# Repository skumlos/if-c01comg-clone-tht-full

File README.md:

IF-C01COMG Clone board THT Full size

This is a full sized version of the IF-C01COMG board for JVC pro monitors (TM-Hxx50CG) and some others...

It's basically the THT base board I made some years ago with SCART or BNC input and some audio mixing
stuff.

Credit goes to James Vanderloeff for the dual input idea.

You can upload the zip file from the plot directory directly to manufacturers that don't do kicad files directly.

You're welcome to clone, sell, re-design and whatever, see LICENSE.

(2020) Martin Hejnfelt (martin@hejnfelt.com)
This work is free. You can redistribute it and/or modify it under the
terms of the Do What The Fuck You Want To Public License, Version 2,
as published by Sam Hocevar. See the LICENSE file for more details.

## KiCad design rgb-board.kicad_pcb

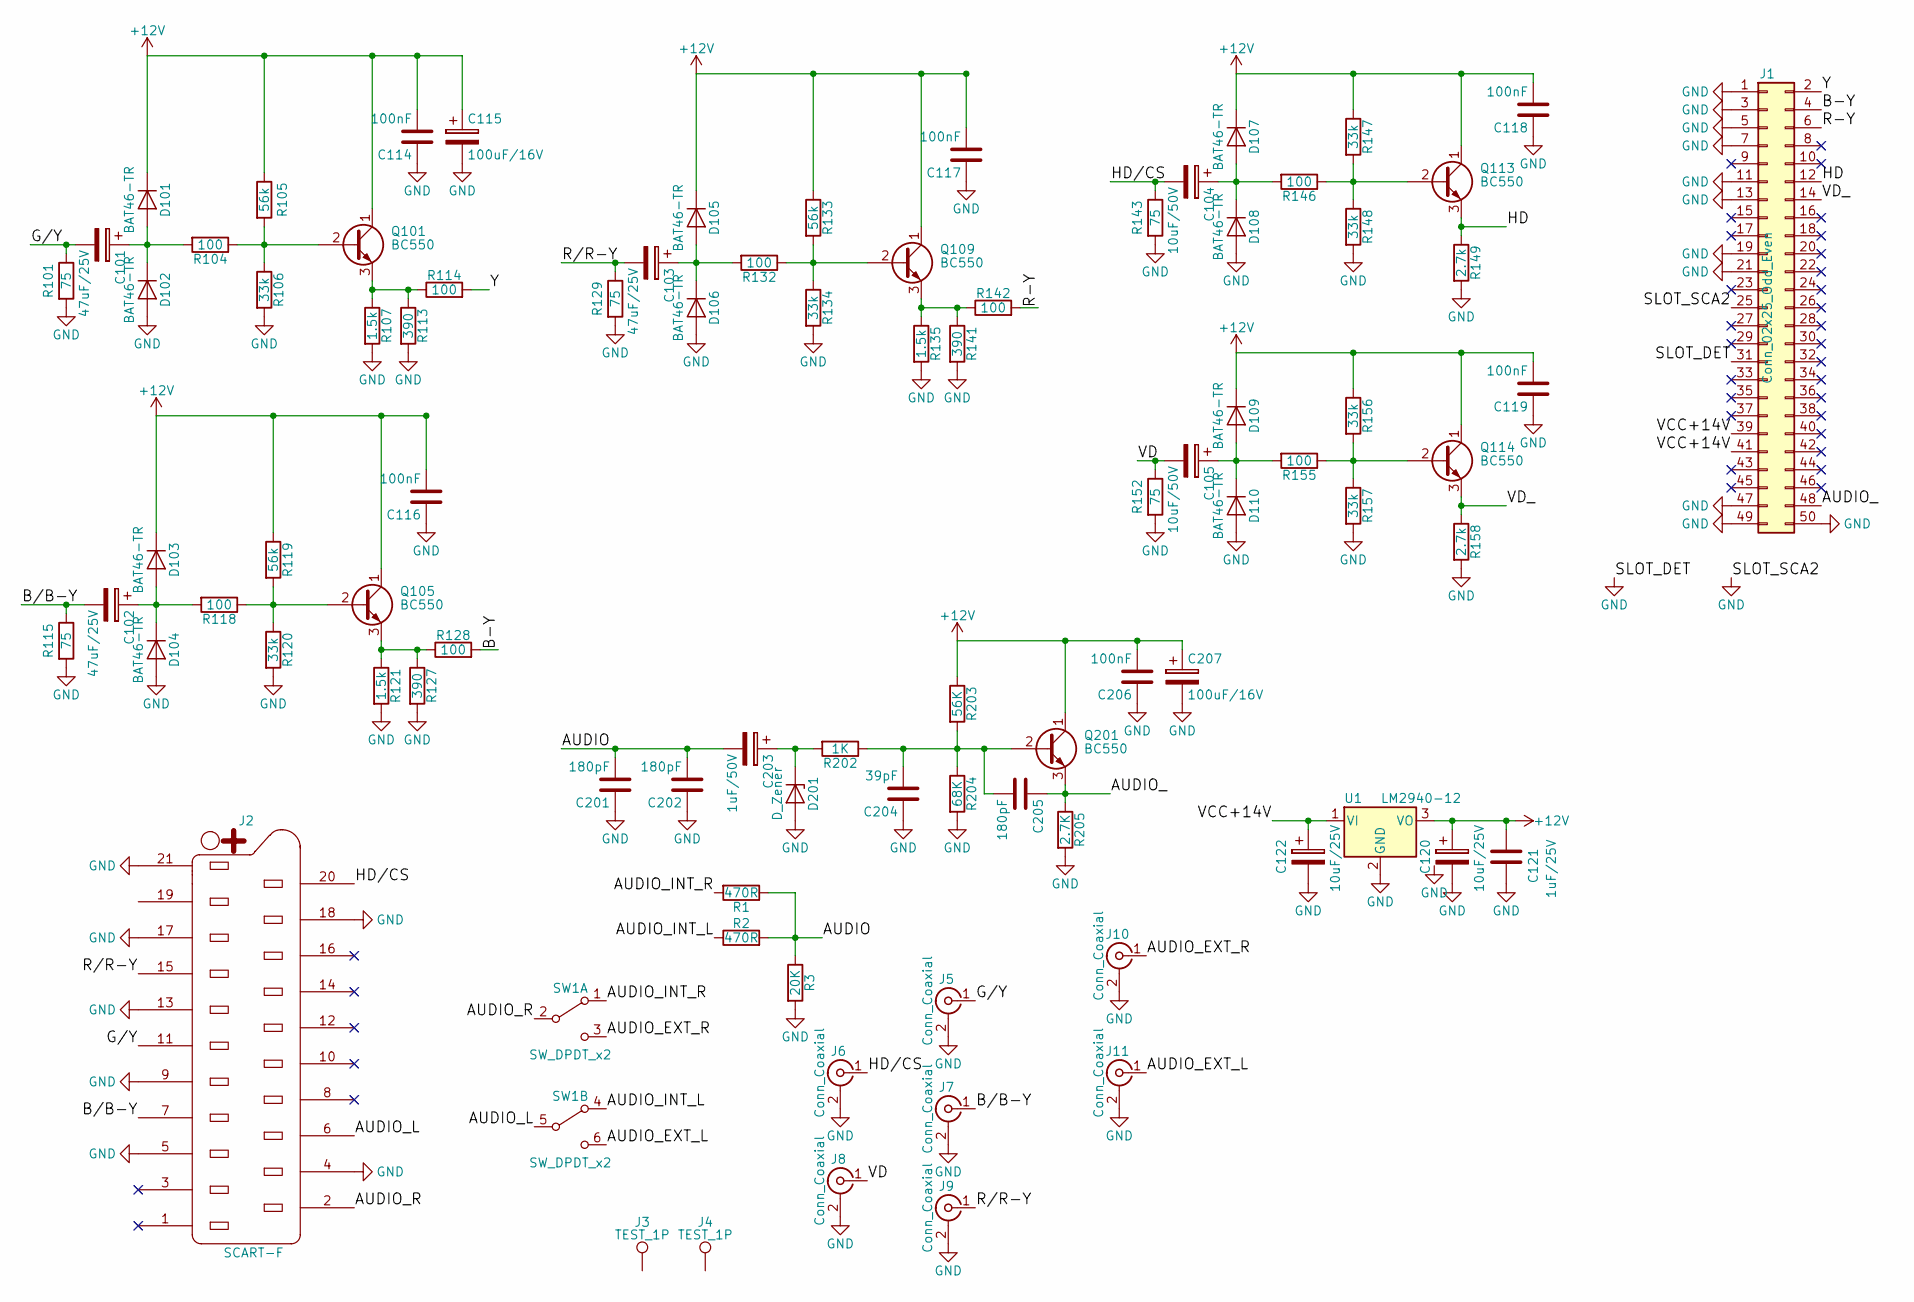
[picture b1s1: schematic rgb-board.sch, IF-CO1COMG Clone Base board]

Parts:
C101, C102, C103: 47uF/25V; CP_Radial_D5.0mm_P2.50mm
C104, C105: 10uF/50V; CP_Radial_D5.0mm_P2.00mm
C114, C116, C117, C118, C119, C206: 100nF; C_Disc_D3.8mm_W2.6mm_P2.50mm
C115, C207: 100uF/16V; CP_Radial_D6.3mm_P2.50mm
C120, C122: 10uF/25V; CP_Radial_D5.0mm_P2.00mm
C121: 1uF/25V; C_Disc_D5.0mm_W2.5mm_P2.50mm
C201, C202, C205: 180pF; C_Disc_D3.8mm_W2.6mm_P2.50mm
C203: 1uF/50V; CP_Radial_D5.0mm_P2.50mm
C204: 39pF; C_Disc_D3.8mm_W2.6mm_P2.50mm
D101, D102, D103, D104, D105, D106, D107, D108, D109, D110: BAT46-TR; D_DO-35_SOD27_P7.62mm_Horizontal
D201: D_Zener; D_DO-35_SOD27_P7.62mm_Horizontal
J1: Conn_02x25_Odd_Even; Pin_Header_Angled_2x25_Pitch2.54mm
J2: SCART-F; NINIGI-SCART-RA
J3, J4: TEST_1P; MountingHole_3.2mm_M3
J5, J6, J7, J8, J9: Conn_Coaxial; BNC-THT
J10, J11: Conn_Coaxial; RCJ-04X
Q101, Q105, Q109, Q113, Q114, Q201: BC550; TO-92_Molded_Narrow
R1, R2: 470R; R_Axial_DIN0207_L6.3mm_D2.5mm_P7.62mm_Horizontal
R3: 20K; R_Axial_DIN0207_L6.3mm_D2.5mm_P7.62mm_Horizontal
R101, R115, R129, R143, R152: 75; R_Axial_DIN0207_L6.3mm_D2.5mm_P7.62mm_Horizontal
R104, R114, R118, R128, R132, R142, R146, R155: 100; R_Axial_DIN0207_L6.3mm_D2.5mm_P7.62mm_Horizontal
R105, R119, R133: 56k; R_Axial_DIN0207_L6.3mm_D2.5mm_P7.62mm_Horizontal
R106, R120, R134, R147, R148, R156, R157: 33k; R_Axial_DIN0207_L6.3mm_D2.5mm_P7.62mm_Horizontal
R107, R121, R135: 1.5k; R_Axial_DIN0207_L6.3mm_D2.5mm_P7.62mm_Horizontal
R113, R127, R141: 390; R_Axial_DIN0207_L6.3mm_D2.5mm_P7.62mm_Horizontal
R149, R158: 2.7k; R_Axial_DIN0207_L6.3mm_D2.5mm_P7.62mm_Horizontal
R202: 1K; R_Axial_DIN0207_L6.3mm_D2.5mm_P7.62mm_Horizontal
R203: 56K; R_Axial_DIN0207_L6.3mm_D2.5mm_P7.62mm_Horizontal
R204: 68K; R_Axial_DIN0207_L6.3mm_D2.5mm_P7.62mm_Horizontal
R205: 2.7K; R_Axial_DIN0207_L6.3mm_D2.5mm_P7.62mm_Horizontal
SW1: SW_DPDT_x2; LC2259
U1: LM2940-12; TO-220_Horizontal

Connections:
+12V: C114.2, C115.1, C116.2, C117.2, C118.2, C119.2, C120.1, C121.2, C206.2, C207.1, D101.1 (K), D103.1 (K), D105.1 (K), D107.1 (K), D109.1 (K), Q101.1 (C), Q105.1 (C), Q109.1 (C), Q113.1 (C), Q114.1 (C), Q201.1 (C), R105.1, R119.1, R133.1, R147.1, R156.1, R203.1, U1.3 (VO)
/AUDIO: C201.2, C202.2, C203.2, R1.1, R2.2, R3.1
/AUDIO_: C205.1, J1.48, Q201.3 (E), R205.1
/AUDIO_EXT_L: J11.1 (In), SW1.6 (C)
/AUDIO_EXT_R: J10.1 (In), SW1.3 (C)
/AUDIO_INT_L: R2.1, SW1.4 (A)
/AUDIO_INT_R: R1.2, SW1.1 (A)
/AUDIO_L: J2.6, SW1.5 (B)
/AUDIO_R: J2.2, SW1.2 (B)
/B-Y: J1.4, R128.2
/B/B-Y: C102.2, J2.7, J7.1 (In), R115.1
/G/Y: C101.2, J2.11, J5.1 (In), R101.1
/HD: J1.12, Q113.3 (E), R149.1
/HD/CS: C104.2, J2.20, J6.1 (In), R143.1
/R-Y: J1.6, R142.2
/R/R-Y: C103.2, J2.15, J9.1 (In), R129.1
/VCC+14V: C122.1, J1.39, J1.41, U1.1 (VI)
/VD: C105.2, J8.1 (In), R152.1
/VD_: J1.14, Q114.3 (E), R158.1
/Y: J1.2, R114.2
GND: C114.1, C115.2, C116.1, C117.1, C118.1, C119.1, C120.2, C121.1, C122.2, C201.1, C202.1, C204.1, C206.1, C207.2, D102.2 (A), D104.2 (A), D106.2 (A), D108.2 (A), D110.2 (A), D201.2 (A), J1.1, J1.3, J1.5, J1.7, J1.11, J1.13, J1.19, J1.21, J1.25, J1.31, J1.47, J1.49, J1.50, J2.4, J2.5, J2.9, J2.13, J2.17, J2.18, J2.21, J5.2 (Ext), J6.2 (Ext), J7.2 (Ext), J8.2 (Ext), J9.2 (Ext), J10.2 (Ext), J11.2 (Ext), R3.2, R101.2, R106.2, R107.2, R113.2, R115.2, R120.2, R121.2, R127.2, R129.2, R134.2, R135.2, R141.2, R143.2, R148.2, R149.2, R152.2, R157.2, R158.2, R204.2, R205.2, U1.2 (GND)
unnamed: C101.1, D101.2 (A), D102.1 (K), R104.2
unnamed: C102.1, D103.2 (A), D104.1 (K), R118.2
unnamed: C103.1, D105.2 (A), D106.1 (K), R132.2
unnamed: C104.1, D107.2 (A), D108.1 (K), R146.2
unnamed: C105.1, D109.2 (A), D110.1 (K), R155.2
unnamed: C203.1, D201.1 (K), R202.2
unnamed: C204.2, C205.2, Q201.2 (B), R202.1, R203.2, R204.1
unnamed: Q101.2 (B), R104.1, R105.2, R106.1
unnamed: Q101.3 (E), R107.1, R113.1, R114.1
unnamed: Q105.2 (B), R118.1, R119.2, R120.1
unnamed: Q105.3 (E), R121.1, R127.1, R128.1
unnamed: Q109.2 (B), R132.1, R133.2, R134.1
unnamed: Q109.3 (E), R135.1, R141.1, R142.1
unnamed: Q113.2 (B), R146.1, R147.2, R148.1
unnamed: Q114.2 (B), R155.1, R156.2, R157.1

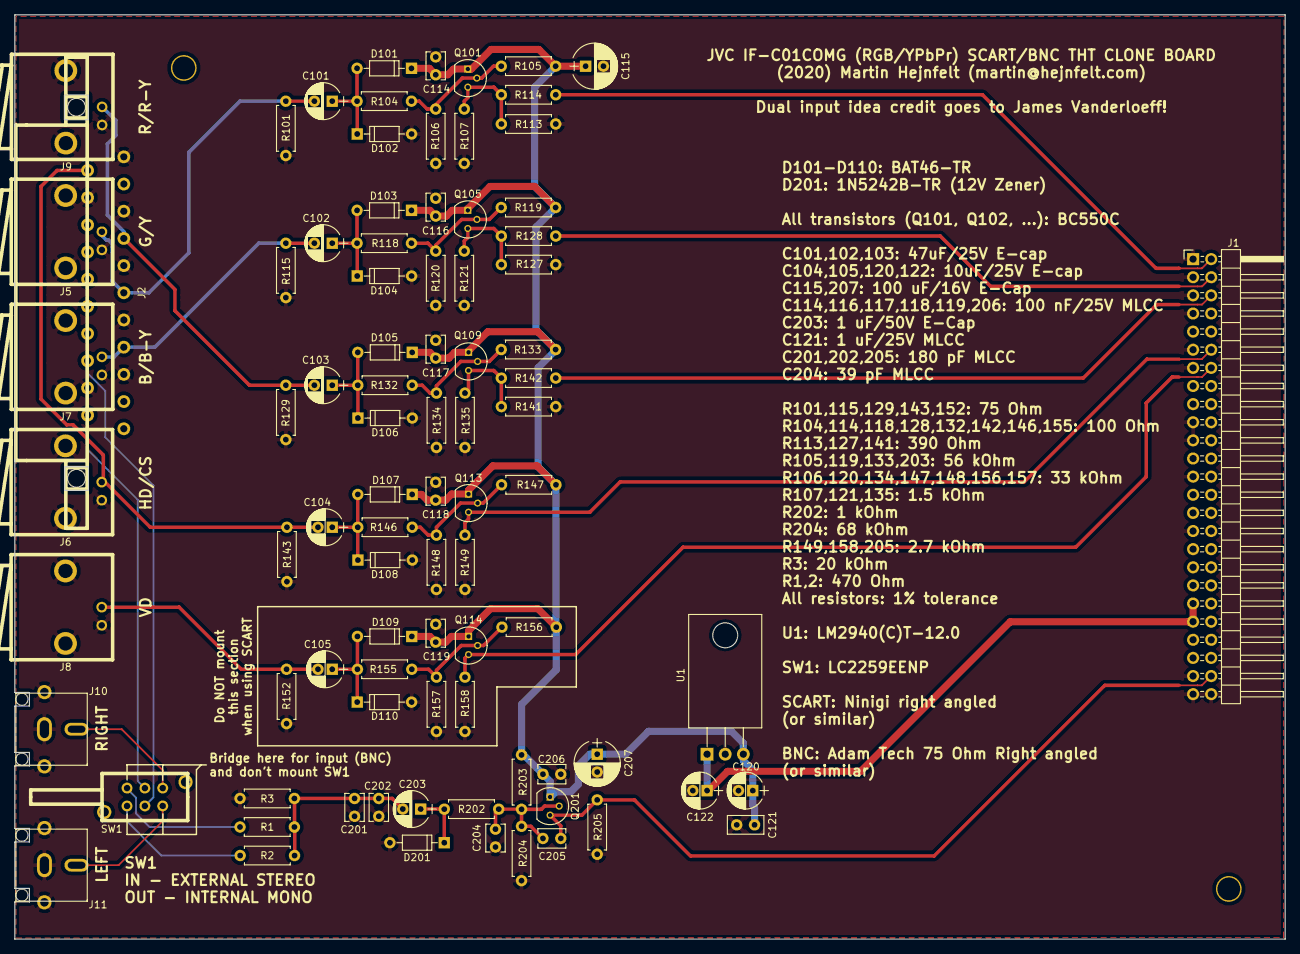
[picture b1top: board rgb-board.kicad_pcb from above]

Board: 2 copper layers, 178.0 x 129.5 mm, 89 parts (0 on the bottom side), 36 nets.

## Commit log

2020-08-26 Moved around a bit
2020-08-26 Added fp-lib-table
2020-08-26 Added plot
2020-08-26 Added license, updated readme
2020-11-05 Fixed missing R155 value
